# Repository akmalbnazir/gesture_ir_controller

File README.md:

# ✋ Gesture-Based IR Controller

This project is a compact, SMD-based **gesture-controlled infrared (IR) transmitter**, powered by the RP2040 microcontroller and the APDS-9960 gesture sensor. It enables hands-free control of IR-enabled devices like TVs, LED strips, or home automation receivers, all without needing Bluetooth, Wi-Fi, or pairing.

---

## 📦 Features

- 🔌 Powered via USB-C (Power-only 6P connector)
- 🧠 Built on the **RP2040** dual-core microcontroller
- 👋 Integrated **APDS-9960** gesture/proximity sensor
- 📤 High-speed IR LED transmission using PWM (38kHz)
- 🔘 Manual **Bootsel** and **Reset** buttons for development
- 🌈 Optional status LED for gesture response indication
- 🔧 Fully SMD design, suitable for hand or reflow soldering

---

## 🔧 Hardware Overview

### 🧠 Core MCU
- **RP2040** with external QSPI Flash (if required)
- Powered via onboard AMS1117-3.3 LDO

### 👋 Gesture Input
- **APDS-9960** optical sensor (I2C)
- INT pin routed to GPIO for real-time gesture notifications
- Pull-up resistors (10kΩ) on SDA and SCL
- Decoupling capacitor (0.1uF) for power stability

### 📤 Infrared Output
- High-efficiency **IR LED**
- Current-limiting resistor (100Ω)
- Driven directly from a GPIO at 38kHz using PWM

### 🧪 Debug / Control
- **SW1**: Bootsel button → GPIO0 (active-low)
- **SW2**: Reset button → RP2040 `RUN` pin (active-low)
- **D1**: Optional status LED (330Ω resistor)

### 🔋 Power Regulation
- **USB-C (Power Only)** input
- **AMS1117-3.3** LDO regulator
- 10uF output capacitor (C2)
- Pull-downs (5.1kΩ) on CC1 and CC2 for proper USB-C sink negotiation

---

## 📐 GPIO Assignments

| Function         | GPIO Pin |
|------------------|----------|
| I2C SDA          | GPIO20   |
| I2C SCL          | GPIO21   |
| Gesture INT      | GPIO22   |
| Status LED       | GPIO23   |
| IR Output (PWM)  | GPIO19   |
| Bootsel (SW1)    | GPIO0    |
| Reset (SW2)      | RUN pin  |

---

## 🛠️ Component Footprints (SMD)

| Component     | Footprint                          |
|---------------|------------------------------------|
| RP2040        | `MCU_RaspberryPi:RP2040`           |
| APDS-9960     | `Sensor_Optical:APDS-9960`         |
| IR LED        | `LED_SMD:LED_0805_2012Metric`      |
| SW1/SW2       | `Button_Switch_SMD:SW_SPST_SKQG`   |
| AMS1117-3.3   | `Regulator_Linear:AMS1117-3.3`     |
| USB-C         | `Connector_USB:USB_C_Receptacle_GCT_USB4125-6P_TopMount_Horizontal` |
| Resistors     | `Resistor_SMD:R_0603_1608Metric`   |
| Capacitors    | `Capacitor_SMD:C_0603_1608Metric`  |

---

## 🧠 Logic Flow

```c
// Pseudocode overview
setup() {
    configure_i2c();
    configure_pwm(38kHz);  // for IR LED
    attach_interrupt(GESTURE_INT);
}

loop() {
    if (gesture == RIGHT_SWIPE) {
        send_ir_code(POWER);
    }
    else if (gesture == UP_SWIPE) {
        send_ir_code(VOLUME_UP);
    }
    // etc.
}
```

---

## 📝 Bill of Materials (Simplified)

| Quantity | Component       | Value    |
|----------|------------------|----------|
| 1x       | RP2040           | –        |
| 1x       | APDS-9960        | –        |
| 1x       | IR LED           | –        |
| 1x       | Status LED       | –        |
| 1x       | AMS1117-3.3      | –        |
| 1x       | USB-C Connector  | 6P       |
| 2x       | Tactile Switch   | –        |
| 2x       | 10kΩ Resistor    | Pull-up  |
| 2x       | 5.1kΩ Resistor   | USB-C CC |
| 1x       | 330Ω Resistor    | LED      |
| 1x       | 100Ω Resistor    | IR LED   |
| 1x       | 0.1uF Capacitor  | –        |
| 1x       | 10uF Capacitor   | –        |

---

## 📁 Folder Structure

```
/Gesture-IR-Controller/
├── schematic.kicad_sch
├── pcb.kicad_pcb
├── symbols/
├── footprints/
├── firmware/  (optional)
└── README.md
```

---

## Preview

---

## 📜 License

This project is released under the **MIT License**.  
Use it freely, improve it, deploy it — just give credit where it’s due.

---

**Built with love by Akmal Nazir**

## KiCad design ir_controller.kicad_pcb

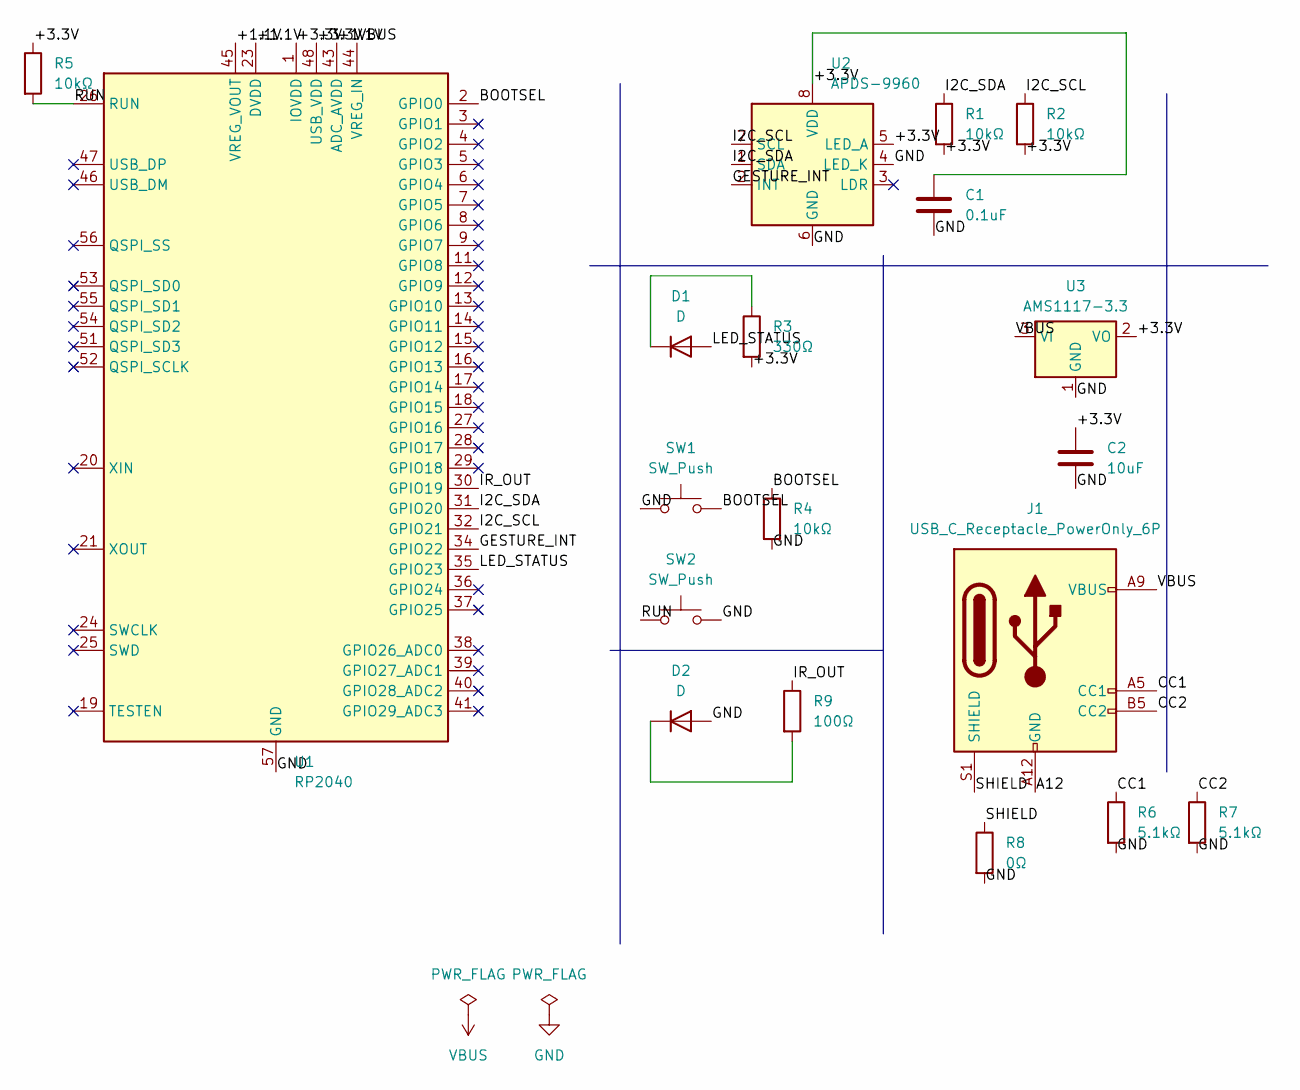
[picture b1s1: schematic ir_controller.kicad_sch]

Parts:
C1: 0.1uF; C_0603_1608Metric
C2: 10uF; C_0603_1608Metric
D1, D2: D; D_0603_1608Metric
J1: USB_C_Receptacle_PowerOnly_6P; USB_C_Receptacle_GCT_USB4125-xx-x-0190_6P_TopMnt_Horizontal
R1, R2, R4, R5: 10kΩ; R_0603_1608Metric
R3: 330Ω; R_0603_1608Metric
R6, R7: 5.1kΩ; R_0603_1608Metric
R8: 0Ω; R_0603_1608Metric
R9: 100Ω; R_0603_1608Metric
SW1, SW2: SW_Push; SW_SPST_SKQG_WithStem
U1: RP2040; QFN-56-1EP_7x7mm_P0.4mm_EP3.2x3.2mm
U2: APDS-9960; Avago_APDS-9960
U3: AMS1117-3.3; SOT-223-3_TabPin2

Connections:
/+1.1V: U1.23 (DVDD), U1.43 (ADC_AVDD), U1.45 (VREG_VOUT), U1.50 (DVDD)
/+3.3V: C1.1, C2.1, R1.2, R2.2, R3.2, R5.1, U1.1 (IOVDD), U1.10 (IOVDD), U1.22 (IOVDD), U1.33 (IOVDD), U1.42 (IOVDD), U1.48 (USB_VDD), U1.49 (IOVDD), U2.5 (LED_A), U2.8 (VDD), U3.2 (VO)
/A12: J1.A12 (GND), J1.B12 (GND)
/BOOTSEL: R4.1, SW1.2, U1.2 (GPIO0)
/CC1: J1.A5 (CC1), R6.1
/CC2: J1.B5 (CC2), R7.1
/GESTURE_INT: U1.34 (GPIO22), U2.2 (INT)
/I2C_SCL: R2.1, U1.32 (GPIO21), U2.7 (SCL)
/I2C_SDA: R1.1, U1.31 (GPIO20), U2.1 (SDA)
/IR_OUT: R9.1, U1.30 (GPIO19)
/LED_STATUS: D1.2 (A), U1.35 (GPIO23)
/RUN: R5.2, SW2.1, U1.26 (RUN)
/SHIELD: J1.S1 (SHIELD), R8.1
GND: C1.2, C2.2, D2.2 (A), R4.2, R6.2, R7.2, R8.2, SW1.1, SW2.2, U1.57 (GND), U2.4 (LED_K), U2.6 (GND), U3.1 (GND)
unnamed: D1.1 (K), R3.1
unnamed: D2.1 (K), R9.2
VBUS: J1.A9 (VBUS), J1.B9 (VBUS), U1.44 (VREG_IN), U3.3 (VI)

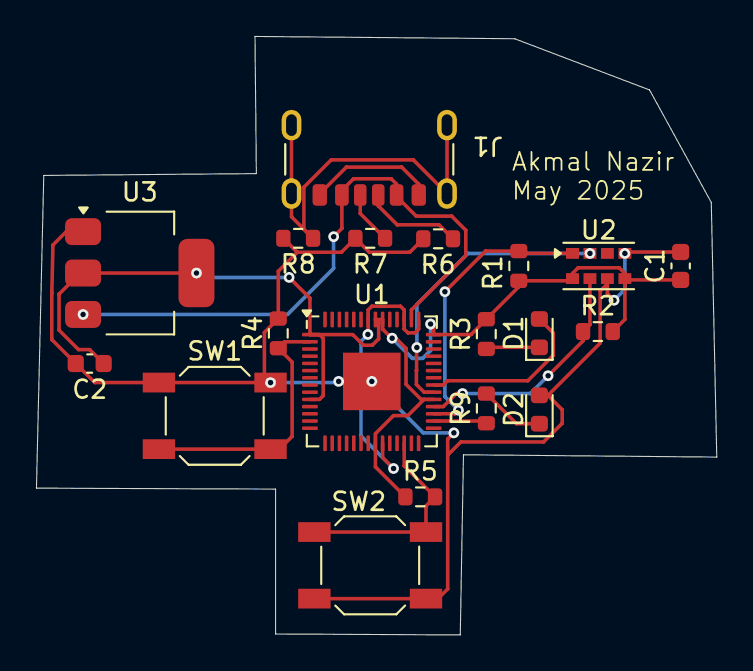
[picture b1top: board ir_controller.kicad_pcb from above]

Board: 2 copper layers, 37.8 x 33.2 mm, 19 parts (0 on the bottom side), 17 nets.
